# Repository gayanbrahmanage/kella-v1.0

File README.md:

# kella-v1.0
 Humonoid Robot Development Project

 ### Base Design and Development
 <div style="display: flex;">

 </div>
 
 ### YouTube Video-Base Manual Mode Testing

[Watch on YouTube](https://www.youtube.com/watch?v=laG0K3bYE8s)

# Design Power Point 

[View Design PPT](photos/pdf.pdf)

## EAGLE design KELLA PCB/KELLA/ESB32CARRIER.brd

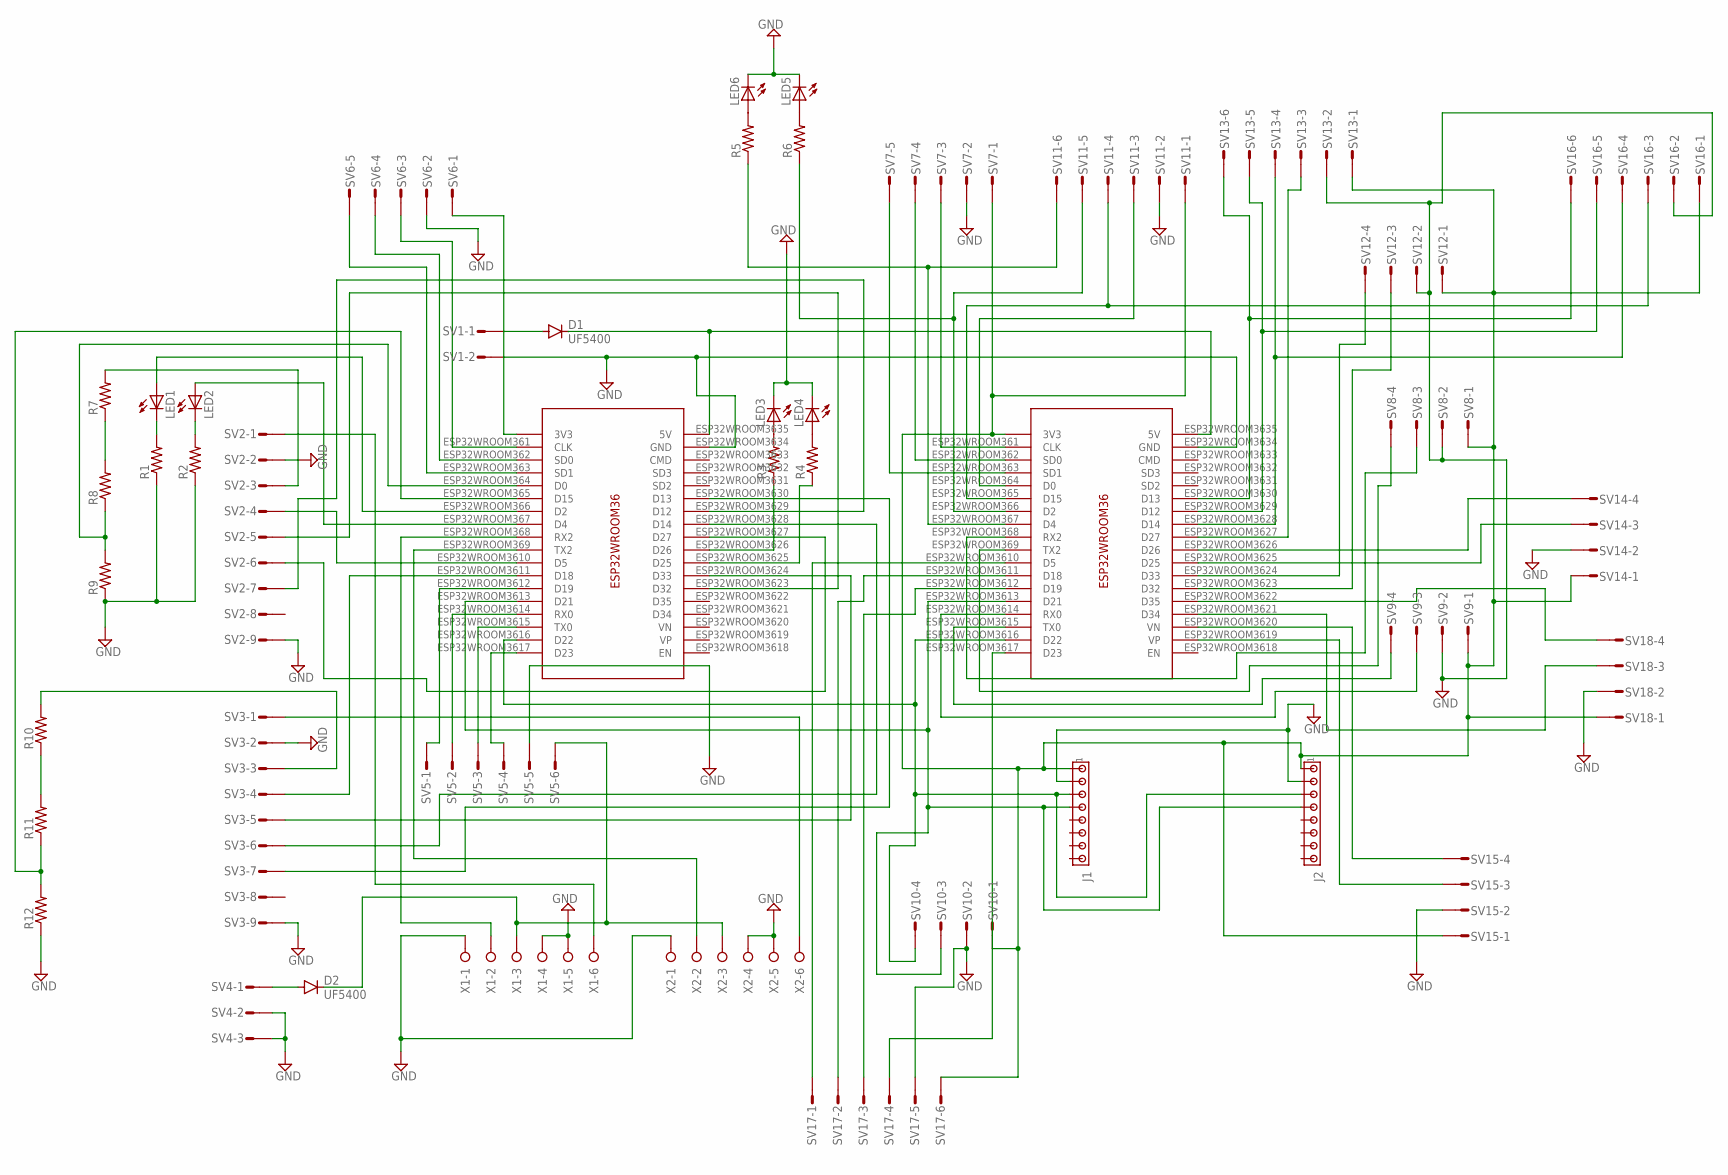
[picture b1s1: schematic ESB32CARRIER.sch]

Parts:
D1, D2: UF5400; DO201-15
J1, J2: MTA08-100; 10X08MTA
LED1, LED2, LED3, LED4, LED5, LED6: LED3MM
R1, R2, R3, R4, R5, R6, R7, R8, R9, R10, R11, R12: R-US_0207/10; 0207/10
SV1: L02P
SV2, SV3: L09P
SV4: L03P
SV5, SV11, SV13, SV16, SV17: L06P
SV6, SV7: L05P
SV8, SV9, SV10, SV12, SV14, SV15, SV18: L04P
U$1, U$2: ESP32WROOM36; ESP32WROOM36PINDIP
X1, X2: W237-06P; W237-6P

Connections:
GND: J1.2, J2.2, LED3.K (C), LED4.K (C), LED5.K (C), LED6.K (C), R1.1, R2.1, R9.1, R12.1, SV1.2, SV2.2, SV2.9, SV3.2, SV3.9, SV4.2, SV4.3, SV5.5, SV6.2, SV7.2, SV8.2, SV9.2, SV10.2, SV11.2, SV12.2, SV13.2, SV14.2, SV15.2, SV16.2, SV17.5, SV18.2, U$1.ESP32WROOM3634 (GND), U$2.ESP32WROOM3634 (GND), X1.1, X1.4, X1.5, X2.1, X2.4, X2.5
unnamed: D1.C, U$1.ESP32WROOM3635 (5V), U$2.ESP32WROOM3635 (5V)
unnamed: SV2.1, X1.6
unnamed: D2.A, SV4.1
unnamed: SV3.1, X2.6
unnamed: R7.1, R8.2
unnamed: SV2.6, U$1.ESP32WROOM3627 (D27)
unnamed: D1.A, SV1.1
unnamed: SV5.1, U$1.ESP32WROOM3612 (D19)
unnamed: SV2.4, U$1.ESP32WROOM3610 (D5)
unnamed: U$1.ESP32WROOM368 (RX2), X1.2
unnamed: U$1.ESP32WROOM369 (TX2), X2.2
unnamed: R7.2, SV2.3
unnamed: R11.1, R12.2, U$1.ESP32WROOM365 (D15)
unnamed: R10.1, R11.2
unnamed: R10.2, SV3.3
unnamed: R8.1, R9.2, U$1.ESP32WROOM364 (D0)
unnamed: SV3.4, U$1.ESP32WROOM3611 (D18)
unnamed: SV2.5, U$1.ESP32WROOM3623 (D32)
unnamed: SV3.5, U$1.ESP32WROOM3624 (D33)
unnamed: SV3.6, U$1.ESP32WROOM3628 (D14)
unnamed: SV2.7, U$1.ESP32WROOM3629 (D12)
unnamed: SV3.7, U$1.ESP32WROOM3630 (D13)
unnamed: J1.1, J2.1, SV7.1, SV8.1, SV9.1, SV10.1, SV11.1, SV12.1, SV13.1, SV14.1, SV15.1, SV16.1, SV17.6, SV18.1, U$2.ESP32WROOM360 (3V3)
unnamed: SV6.1, U$1.ESP32WROOM360 (3V3)
unnamed: SV7.5, U$2.ESP32WROOM363 (SD1)
unnamed: J1.3, J2.3, SV10.4, U$1.ESP32WROOM3616 (D22), U$2.ESP32WROOM3616 (D22)
unnamed: J1.4, J2.4, SV10.3, U$1.ESP32WROOM3613 (D21), U$2.ESP32WROOM3613 (D21)
unnamed: SV17.1, U$2.ESP32WROOM3610 (D5)
unnamed: SV6.5, U$1.ESP32WROOM363 (SD1)
unnamed: SV6.4, U$1.ESP32WROOM362 (SD0)
unnamed: SV6.3, U$1.ESP32WROOM361 (CLK)
unnamed: SV7.4, U$2.ESP32WROOM362 (SD0)
unnamed: SV7.3, U$2.ESP32WROOM361 (CLK)
unnamed: SV9.3, U$2.ESP32WROOM3614 (RX0)
unnamed: SV9.4, U$2.ESP32WROOM3615 (TX0)
unnamed: SV13.6, SV16.6, U$2.ESP32WROOM3630 (D13)
unnamed: SV13.5, SV16.5, U$2.ESP32WROOM3629 (D12)
unnamed: SV8.4, U$2.ESP32WROOM369 (TX2)
unnamed: SV8.3, U$2.ESP32WROOM368 (RX2)
unnamed: SV11.3, U$2.ESP32WROOM364 (D0)
unnamed: SV11.4, SV16.3, U$2.ESP32WROOM365 (D15)
unnamed: R6.1, SV11.5, U$2.ESP32WROOM366 (D2)
unnamed: R5.1, SV11.6, U$2.ESP32WROOM367 (D4)
unnamed: SV12.3, U$2.ESP32WROOM3623 (D32)
unnamed: SV12.4, U$2.ESP32WROOM3624 (D33)
unnamed: SV13.4, SV16.4, U$2.ESP32WROOM3628 (D14)
unnamed: SV13.3, U$2.ESP32WROOM3627 (D27)
unnamed: SV17.2, U$2.ESP32WROOM3611 (D18)
unnamed: SV14.4, U$2.ESP32WROOM3626 (D26)
unnamed: SV14.3, U$2.ESP32WROOM3625 (D25)
unnamed: SV15.4, U$2.ESP32WROOM3620 (VN)
unnamed: SV15.3, U$2.ESP32WROOM3619 (VP)
unnamed: SV17.3, U$2.ESP32WROOM3612 (D19)
unnamed: SV17.4, U$2.ESP32WROOM3617 (D23)
unnamed: SV5.4, U$1.ESP32WROOM3617 (D23)
unnamed: SV5.2, U$1.ESP32WROOM3614 (RX0)
unnamed: D2.C, SV5.6, X1.3, X2.3
unnamed: LED3.A, R3.2
unnamed: SV5.3, U$1.ESP32WROOM3615 (TX0)
unnamed: LED1.K (C), R1.2
unnamed: LED2.K (C), R2.2
unnamed: LED1.A, U$1.ESP32WROOM366 (D2)
unnamed: LED2.A, U$1.ESP32WROOM367 (D4)
unnamed: LED4.A, R4.2
unnamed: R3.1, U$1.ESP32WROOM3626 (D26)
unnamed: R4.1, U$1.ESP32WROOM3625 (D25)
unnamed: LED6.A, R5.2
unnamed: SV18.4, U$2.ESP32WROOM3622 (D35)
unnamed: SV18.3, U$2.ESP32WROOM3621 (D34)
unnamed: LED5.A, R6.2

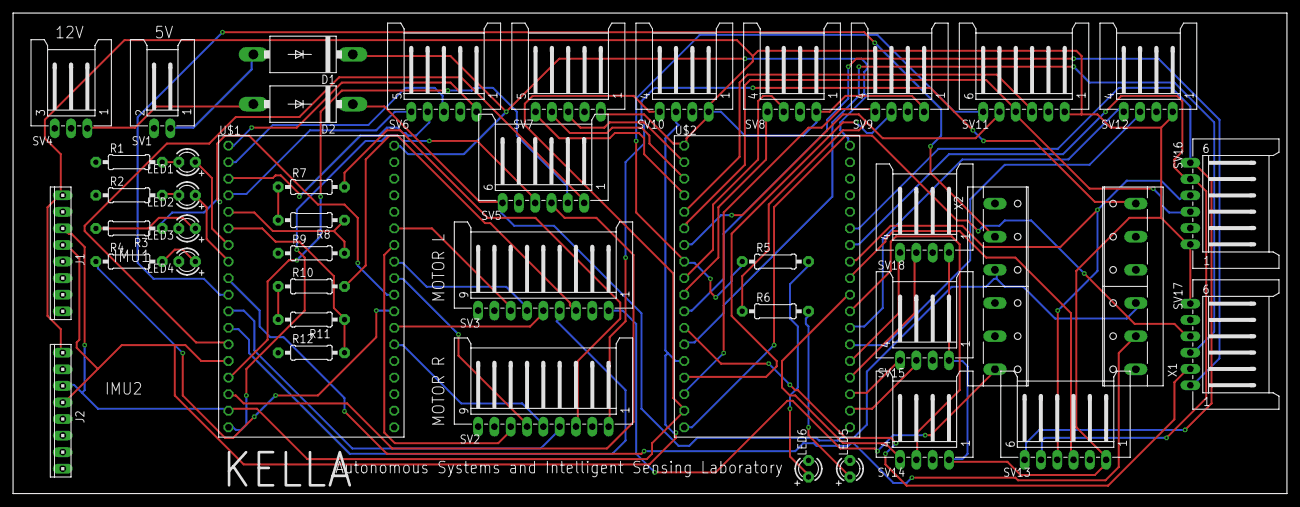
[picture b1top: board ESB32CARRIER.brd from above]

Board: 2 copper layers, 195.2 x 73.7 mm, 44 parts (0 on the bottom side), 71 nets.

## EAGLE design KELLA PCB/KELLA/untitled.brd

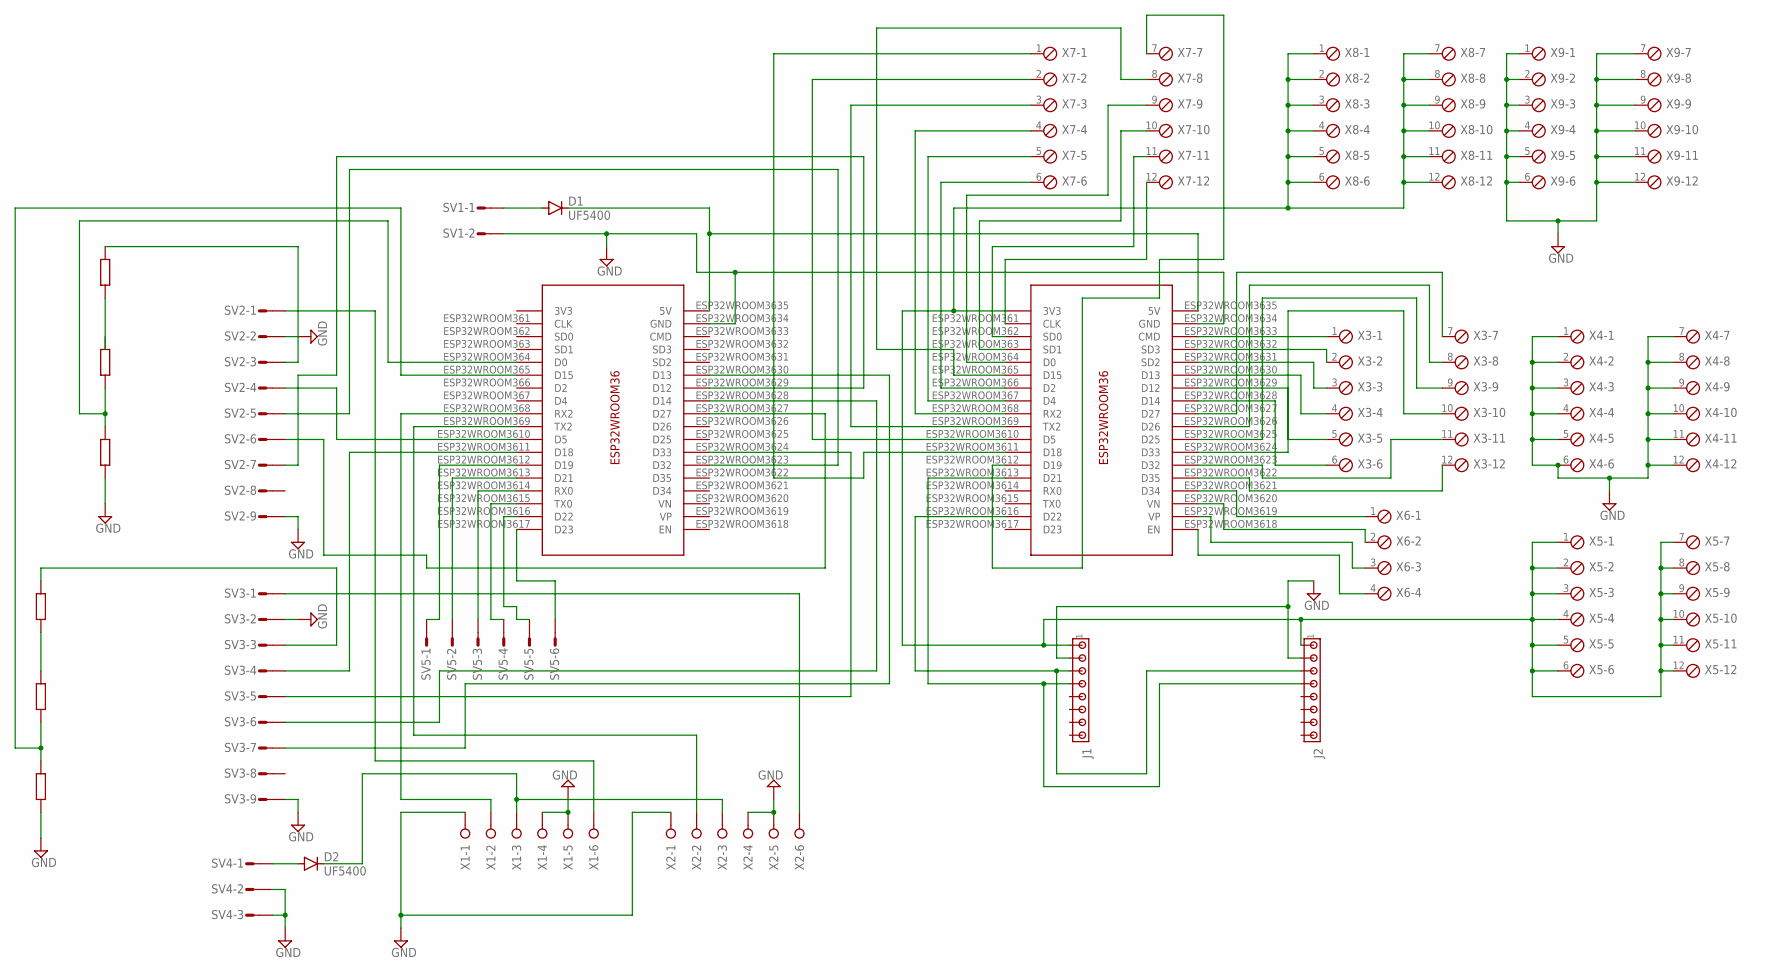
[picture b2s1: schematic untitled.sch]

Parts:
D1, D2: UF5400; DO201-15
J1, J2: MTA08-100; 10X08MTA
SV1: L02P
SV2, SV3: L09P
SV4: L03P
SV5: L06P
U$1, U$2: ESP32WROOM36; ESP32WROOM36PINDIP
X1, X2: W237-06P; W237-6P
X3, X4, X5, X7, X8, X9: MPT12; 12POL254
X6: MPT4; 4POL254

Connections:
GND: J1.2, J2.2, SV1.2, SV2.2, SV2.9, SV3.2, SV3.9, SV4.2, SV4.3, U$1.ESP32WROOM3634 (GND), U$2.ESP32WROOM3634 (GND), X1.1, X1.4, X1.5, X2.1, X2.4, X2.5, X4.1, X4.2, X4.3, X4.4, X4.5, X4.6, X4.7, X4.8, X4.9, X4.10, X4.11, X4.12, X9.1, X9.2, X9.3, X9.4, X9.5, X9.6, X9.7, X9.8, X9.9, X9.10, X9.11, X9.12
unnamed: D1.C, U$1.ESP32WROOM3635 (5V), U$2.ESP32WROOM3635 (5V)
unnamed: SV2.1, X1.6
unnamed: D2.A, SV4.1
unnamed: SV3.1, X2.6
unnamed: SV2.6, U$1.ESP32WROOM3627 (D27)
unnamed: D1.A, SV1.1
unnamed: D2.C, X1.3, X2.3
unnamed: SV2.4, U$1.ESP32WROOM3610 (D5)
unnamed: U$1.ESP32WROOM368 (RX2), X1.2
unnamed: U$1.ESP32WROOM369 (TX2), X2.2
unnamed: SV3.4, U$1.ESP32WROOM3611 (D18)
unnamed: SV2.5, U$1.ESP32WROOM3623 (D32)
unnamed: SV3.5, U$1.ESP32WROOM3624 (D33)
unnamed: SV3.6, U$1.ESP32WROOM3628 (D14)
unnamed: SV2.7, U$1.ESP32WROOM3629 (D12)
unnamed: SV3.7, U$1.ESP32WROOM3630 (D13)
unnamed: J1.1, J2.1, U$2.ESP32WROOM360 (3V3), X5.1, X5.2, X5.3, X5.4, X5.5, X5.6, X5.7, X5.8, X5.9, X5.10, X5.11, X5.12, X8.1, X8.2, X8.3, X8.4, X8.5, X8.6, X8.7, X8.8, X8.9, X8.10, X8.11, X8.12
unnamed: U$2.ESP32WROOM3631 (SD2), X3.3
unnamed: U$2.ESP32WROOM3630 (D13), X3.4
unnamed: J1.3, J2.3, U$2.ESP32WROOM3616 (D22)
unnamed: J1.4, J2.4, U$2.ESP32WROOM3613 (D21)
unnamed: U$2.ESP32WROOM3629 (D12), X3.5
unnamed: U$2.ESP32WROOM3628 (D14), X3.6
unnamed: U$2.ESP32WROOM3633 (CMD), X3.1
unnamed: U$2.ESP32WROOM3632 (SD3), X3.2
unnamed: U$2.ESP32WROOM3627 (D27), X3.7
unnamed: U$2.ESP32WROOM3626 (D26), X3.8
unnamed: U$2.ESP32WROOM3625 (D25), X3.9
unnamed: U$2.ESP32WROOM3624 (D33), X3.10
unnamed: U$2.ESP32WROOM3623 (D32), X3.11
unnamed: U$2.ESP32WROOM3622 (D35), X3.12
unnamed: U$2.ESP32WROOM3621 (D34), X6.1
unnamed: U$2.ESP32WROOM3620 (VN), X6.2
unnamed: U$2.ESP32WROOM3619 (VP), X6.3
unnamed: U$2.ESP32WROOM361 (CLK), X7.12
unnamed: U$2.ESP32WROOM3618 (EN), X6.4
unnamed: U$2.ESP32WROOM362 (SD0), X7.11
unnamed: U$2.ESP32WROOM363 (SD1), X7.10
unnamed: U$2.ESP32WROOM364 (D0), X7.9
unnamed: U$2.ESP32WROOM366 (D2), X7.6
unnamed: U$2.ESP32WROOM367 (D4), X7.5
unnamed: U$2.ESP32WROOM368 (RX2), X7.4
unnamed: U$2.ESP32WROOM369 (TX2), X7.3
unnamed: U$2.ESP32WROOM3610 (D5), X7.2
unnamed: U$2.ESP32WROOM3611 (D18), X7.1
unnamed: U$2.ESP32WROOM365 (D15), X7.8
unnamed: U$2.ESP32WROOM3612 (D19), X7.7
unnamed: SV5.1, U$1.ESP32WROOM3612 (D19)
unnamed: SV5.2, U$1.ESP32WROOM3613 (D21)
unnamed: SV5.3, U$1.ESP32WROOM3614 (RX0)
unnamed: SV5.6, U$1.ESP32WROOM3617 (D23)
unnamed: SV5.5, U$1.ESP32WROOM3616 (D22)
unnamed: SV5.4, U$1.ESP32WROOM3615 (TX0)

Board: 2 copper layers, 20 parts (0 on the bottom side), 54 nets, no tracks yet.

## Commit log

2024-05-02 Added pcb files
2024-08-21 Changed pcb to KiCAD
2024-08-21 updated PCB
2024-08-21 Picture esp32 added
2024-08-22 Added soldered
2024-08-22 Added printed PCB
2024-08-29 Added photos
2024-08-29 Photo Added
2024-08-30 Added PPT
2024-09-04 Esp32code updated
2024-09-06 added x4-3
2024-09-08 Myactuator test added
2024-09-28 CPP CAN added
2024-10-03 CPP updated
